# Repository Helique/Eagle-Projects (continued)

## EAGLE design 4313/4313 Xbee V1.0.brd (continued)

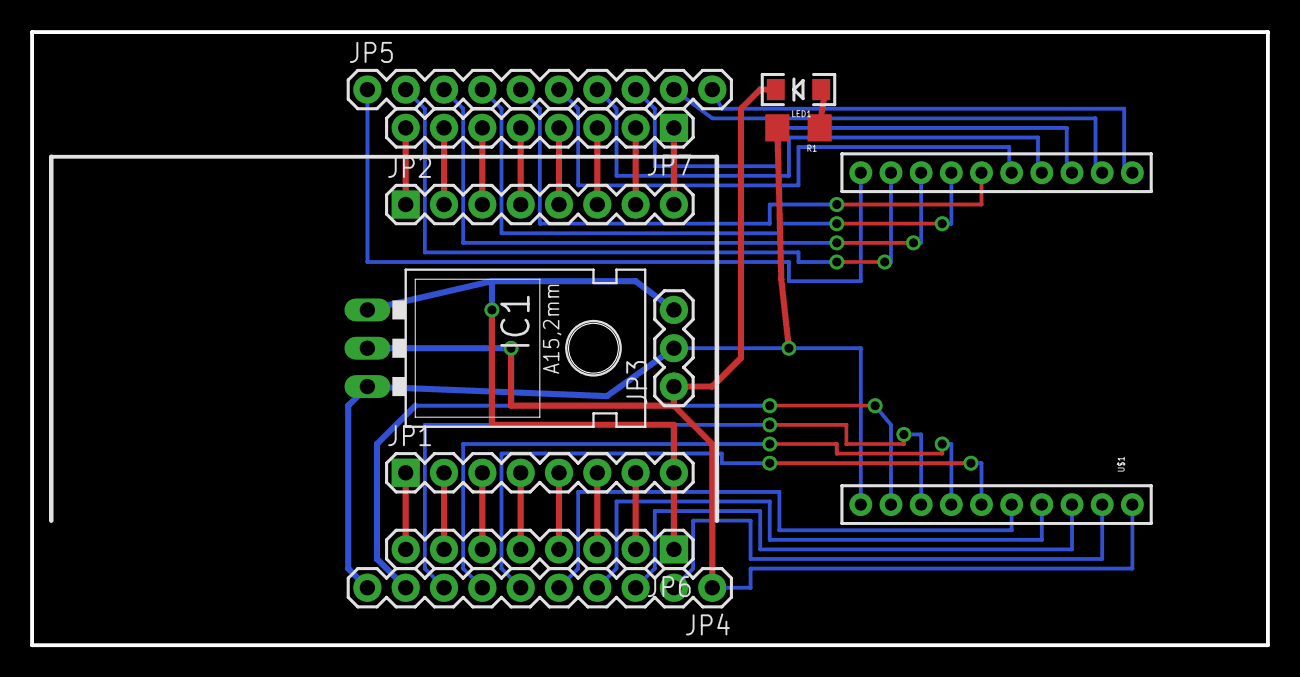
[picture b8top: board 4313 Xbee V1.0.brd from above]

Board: 2 copper layers, 81.9 x 40.6 mm, 11 parts (0 on the bottom side), 37 nets.

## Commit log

2014-11-25 ignore temp board saves
2014-11-25 Revert "ignore temp board saves"
    This reverts commit e6a3784cda25c00734ec2f58f4ecf9e3208dd3f1.
2014-11-25 Initial Commit of my Eagle Projects
2014-12-11 Updates to most boards
2015-12-17 Added schematic for crossover
2015-12-17 Finished Crossover Network Board
2015-12-23 Not Quite sure what is different, but there are the new files. :P
2016-10-15 Fixed incorrect usage of op-amp on pre-amplifier.
